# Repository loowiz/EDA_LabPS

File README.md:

# EDA_LabPS

This is a power supply project based on the chinese DIY kit "0-30V 2mA-3A Adjustable DC Regulated Power Supply".

You can see the "iBom" page here: https://loowiz.github.io/EDA_LabPS/bom/ibom.html

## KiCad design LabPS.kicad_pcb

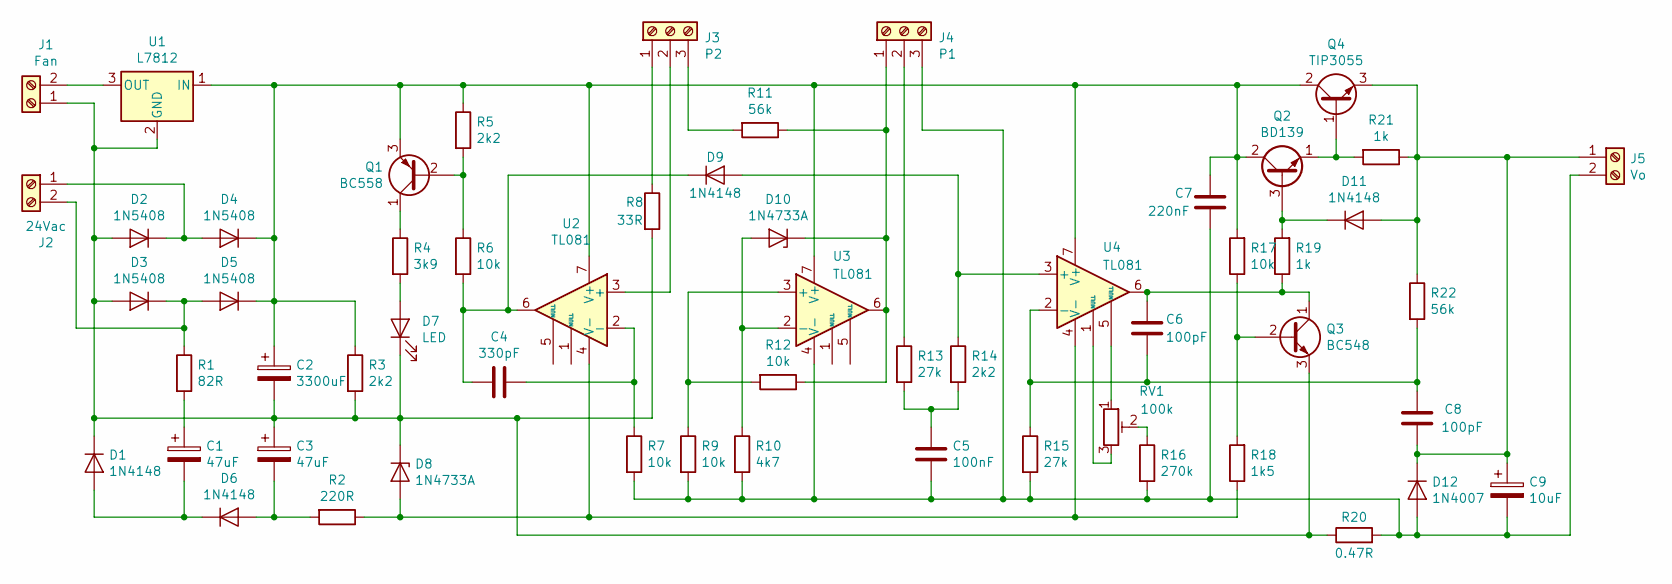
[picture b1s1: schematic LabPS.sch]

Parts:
C1, C3: 47uF; C_Radial_D5.0mm_H11.0mm_P2.00mm
C2: 3300uF; C_Radial_D18.0mm_H35.5mm_P7.50mm
C4: 330pF; C_Disc_D5.0mm_W2.5mm_P5.00mm
C5: 100nF; C_Rect_L13.5mm_W5.0mm_P10.00mm_FKS3_FKP3_MKS4
C6, C8: 100pF; C_Disc_D5.0mm_W2.5mm_P5.00mm
C7: 220nF; C_Rect_L13.5mm_W5.0mm_P10.00mm_FKS3_FKP3_MKS4
C9: 10uF; C_Radial_D5.0mm_H11.0mm_P2.00mm
D1, D6, D9, D11: 1N4148; D_DO-35_SOD27_P7.62mm_Horizontal
D2, D3, D4, D5: 1N5408; D_DO-201AD_P15.24mm_Horizontal
D7: LED; LED_D5.0mm
D8, D10: 1N4733A; D_DO-41_SOD81_P10.16mm_Horizontal
D12: 1N4007; D_DO-41_SOD81_P10.16mm_Horizontal
J1: Fan; PinHeader_1x02_P2.54mm_Vertical
J2: 24Vac; TerminalBlock_bornier-2_P5.08mm
J3: P2; PinHeader_1x03_P2.54mm_Vertical
J4: P1; PinHeader_1x03_P2.54mm_Vertical
J5: Vo; TerminalBlock_bornier-2_P5.08mm
Q1: BC558; TO-92_Inline
Q2: BD139; TO-126-3_Vertical
Q3: BC548; TO-92_Inline
Q4: TIP3055; TO-218-3_Vertical
R1: 82R; R_Axial_DIN0309_L9.0mm_D3.2mm_P12.70mm_Horizontal
R2: 220R; R_Axial_DIN0309_L9.0mm_D3.2mm_P12.70mm_Horizontal
R3: 2k2; R_Axial_DIN0614_L14.3mm_D5.7mm_P15.24mm_Horizontal
R4: 3k9; R_Axial_DIN0207_L6.3mm_D2.5mm_P10.16mm_Horizontal
R5, R14: 2k2; R_Axial_DIN0207_L6.3mm_D2.5mm_P10.16mm_Horizontal
R6, R7, R9, R12, R17: 10k; R_Axial_DIN0207_L6.3mm_D2.5mm_P10.16mm_Horizontal
R8: 33R; R_Axial_DIN0207_L6.3mm_D2.5mm_P10.16mm_Horizontal
R10: 4k7; R_Axial_DIN0207_L6.3mm_D2.5mm_P10.16mm_Horizontal
R11, R22: 56k; R_Axial_DIN0207_L6.3mm_D2.5mm_P10.16mm_Horizontal
R13, R15: 27k; R_Axial_DIN0207_L6.3mm_D2.5mm_P10.16mm_Horizontal
R16: 270k; R_Axial_DIN0207_L6.3mm_D2.5mm_P10.16mm_Horizontal
R18: 1k5; R_Axial_DIN0207_L6.3mm_D2.5mm_P10.16mm_Horizontal
R19, R21: 1k; R_Axial_DIN0207_L6.3mm_D2.5mm_P10.16mm_Horizontal
R20: 0.47R; R_Axial_Power_L25.0mm_W9.0mm_P30.48mm
RV1: 100k; Potentiometer_Bourns_3296Z_Horizontal
U1: L7812; TO-220-3_Vertical
U2, U3, U4: TL081; DIP-8_W7.62mm

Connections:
unnamed: C1.1, R1.2
unnamed: C1.2, D1.2 (A), D6.1 (K)
unnamed: C2.1, C7.2, D4.1 (K), D5.1 (K), Q1.3 (E), Q2.2 (C), Q4.2 (C), R3.1, R5.1, R17.2, U1.1 (IN), U2.7 (V+), U3.7 (V+), U4.7 (V+)
unnamed: C2.2, C3.1, D1.1 (K), D2.2 (A), D3.2 (A), D7.1 (K), D8.1 (K), J1.1, Q3.3 (E), R3.2, R8.2, R20.1, U1.2 (GND)
unnamed: C3.2, D6.2 (A), R2.2
unnamed: C4.1, R7.1, U2.2 (-)
unnamed: C4.2, D9.1 (K), R6.2, U2.6
unnamed: C5.1, C7.1, C9.2, D12.2 (A), J4.3, J5.2, R7.2, R9.2, R10.2, R15.2, R16.2, R20.2, U3.4 (V-)
unnamed: C5.2, R13.2, R14.2
unnamed: C6.1, C8.1, R15.1, R22.2, U4.2 (-)
unnamed: C6.2, Q3.1 (C), R19.1, U4.6
unnamed: C8.2, C9.1, D11.2 (A), D12.1 (K), J5.1, Q4.3 (E), R21.1, R22.1
unnamed: D2.1 (K), D4.2 (A), J2.1
unnamed: D3.1 (K), D5.2 (A), J2.2, R1.1
unnamed: D7.2 (A), R4.2
unnamed: D8.2 (A), R2.1, R18.1, U2.4 (V-), U4.4 (V-)
unnamed: D9.2 (A), R14.1, U4.3 (+)
unnamed: D10.1 (K), J4.1, R11.1, R12.1, U3.6
unnamed: D10.2 (A), R10.1, U3.2 (-)
unnamed: D11.1 (K), Q2.3 (B), R19.2
unnamed: J1.2, U1.3 (OUT)
unnamed: J3.1, R8.1
unnamed: J3.2, U2.3 (+)
unnamed: J3.3, R11.2
unnamed: J4.2, R13.1
unnamed: Q1.1 (C), R4.1
unnamed: Q1.2 (B), R5.2, R6.1
unnamed: Q2.1 (E), Q4.1 (B), R21.2
unnamed: Q3.2 (B), R17.1, R18.2
unnamed: R9.1, R12.2, U3.3 (+)
unnamed: R16.1, RV1.2
unnamed: RV1.1, U4.5 (NULL)
unnamed: RV1.3, U4.1 (NULL)

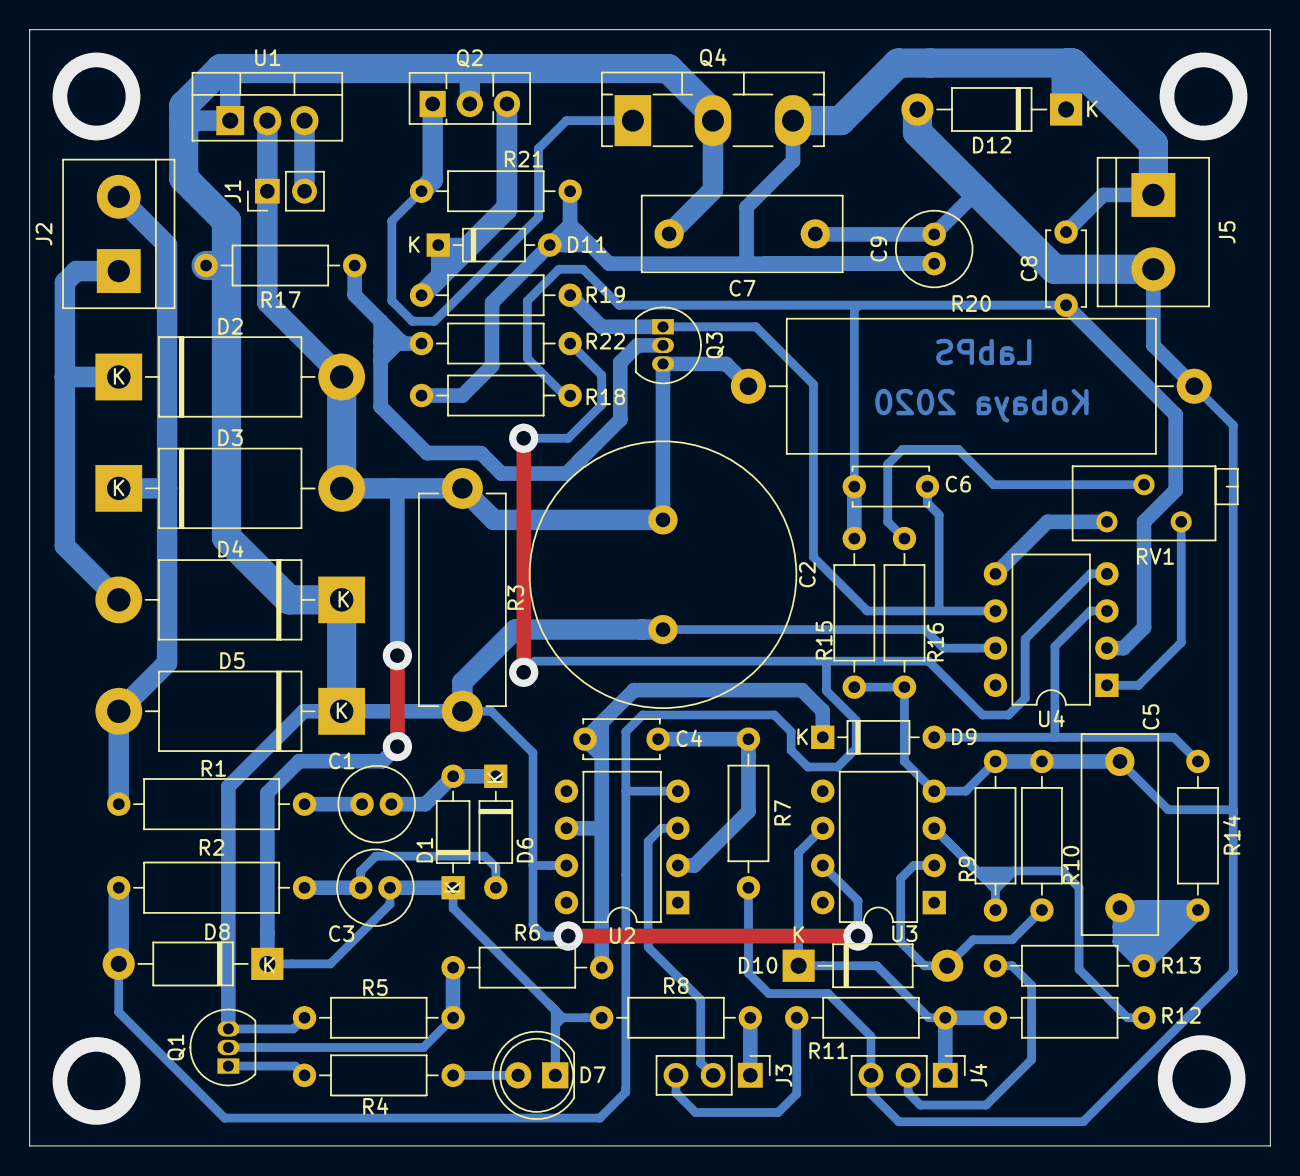
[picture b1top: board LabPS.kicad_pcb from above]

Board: 2 copper layers, 84.8 x 76.3 mm, 57 parts (0 on the bottom side), 33 nets.

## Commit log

2020-07-07 First schematic capture.
2020-07-07 Changes on README.md file.
2020-07-08 Schematic review and footprints added.
2020-07-12 Final PCB layout.
2020-07-12 Set theme jekyll-theme-slate
